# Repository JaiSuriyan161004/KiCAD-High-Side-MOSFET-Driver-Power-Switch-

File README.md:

# High-Side MOSFET Solid-State Switch PCB Prototype

A discrete power electronics hardware layout and component validation project implementing a logic-level triggered, high-side power switching architecture for high-current DC loads, featuring strict front/back electrical layer isolation.

## Project Overview & Technical Scope
The goal of this design was to transition from mechanical switching arrays to solid-state load isolation topologies using KiCad EDA. The circuit employs a logic-level P-channel MOSFET paired with a small-signal N-channel MOSFET driver network to switch a high-current 12V DC barrel jack output line safely. This structure allows low-voltage, low-current microcontroller pins (3.3V/5V logic) to isolate and actuate heavy inductive or resistive DC peripheral loads without exposing control logic to high-power rails.

## Core Engineering Objectives
* **Double-Sided Power & Signal Isolation Layout:** Implemented a strict component separation strategy to optimize noise immunity and thermal performance. **High-current power delivery components are populated exclusively on the front layer**, while **low-power control signal elements are placed entirely on the back layer**. This distinct physical partitioning prevents high-current return loops from corrupting weak control logic lines.
* **Semiconductor Parametric Optimization:** Evaluated manufacturer datasheets to analyze critical transfer characteristics, balancing Gate-Source Threshold Voltage ($V_{GS(th)}$) and Static Drain-Source On-Resistance ($R_{DS(on)}$) curves. This ensures full channel saturation from weak logic inputs to prevent thermal runaway.
* **Over-Engineering & Safety Margin Analysis:** Practiced safe industrial power design methods by picking power components whose Drain-Source Voltage ($V_{DS}$) and continuous drain current ($I_D$) limits exceed maximum load requirements by a strict 2x engineering safety factor.
* **Thermal Architecture & Packaging Design:** Studied the thermal layout profiles of Through-Hole Technology (THT) vs. Surface Mount Devices (SMD). Addressed thermal dissipation constraints by comparing bulky TO-220 packages against compact DPAK/SOIC-8 footprints that utilize dedicated PCB copper pours as thermal heatsinks.
* **Geometric Power Trace Layout:** Configured high-current routing lines with widened trace cross-sections to minimize parasitic resistance and voltage drops across primary power delivery tracks.

## Project Status: Design Phase (Digital Prototype)
*Note: This project is maintained digitally within KiCad to validate custom design rules, trace geometries, and schematic-to-board footprint synchronizations prior to physical prototyping loops.*

---

## Design Visual Previews

### 1. Circuit Schematic Diagram
*Capture of the high-side power distribution configuration, small-signal control isolation layer, and input/output DC terminals.*

### 2. 3D Visual Board Render (Front View - Power Stage)
*Complete 3D structural render showing power footprint clearances, structural trace widths, and heavy-current hardware components populated on the primary layer.*

### 3. 3D Visual Board Render (Back View - Low Power Logic Stage)
*Complete 3D structural render showing the reverse side of the board dedicated entirely to clean, low-current logic and control signal traces.*

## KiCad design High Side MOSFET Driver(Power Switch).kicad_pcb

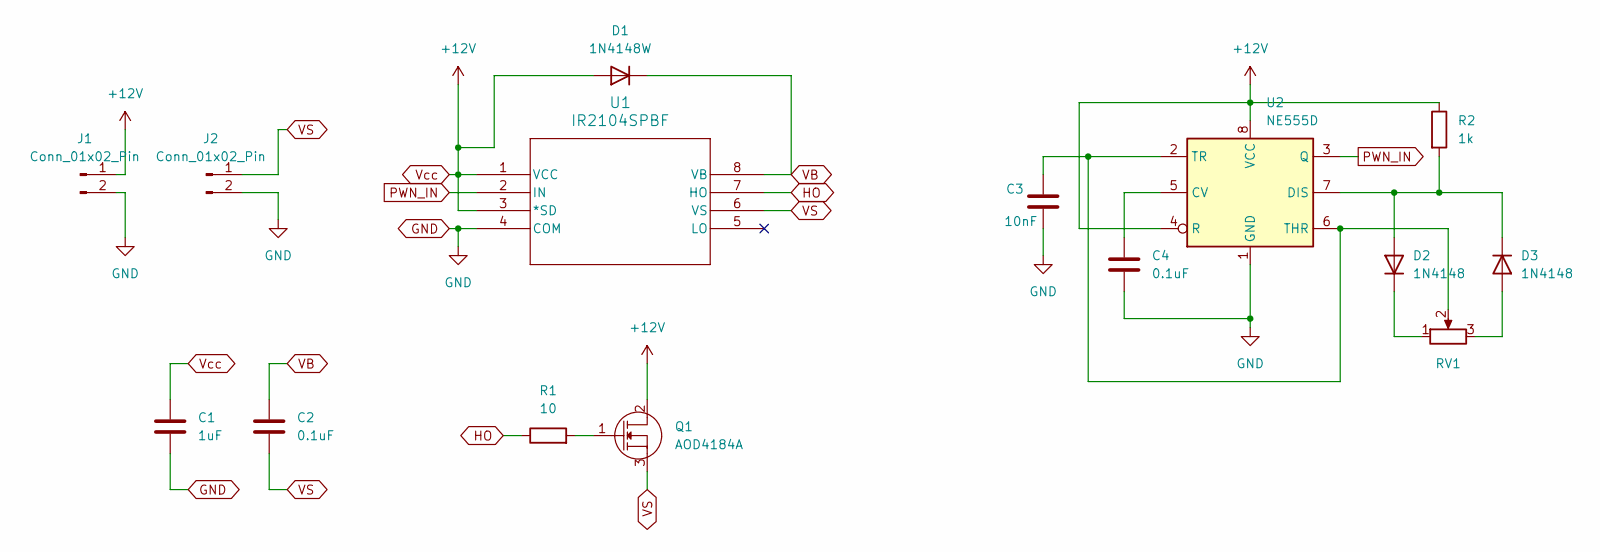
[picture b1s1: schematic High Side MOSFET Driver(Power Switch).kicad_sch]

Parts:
C1: 1uF; C_0201_0603Metric
C2, C4: 0.1uF; C_0201_0603Metric
C3: 10nF; C_0201_0603Metric
D1: 1N4148W; D_SOD-123
D2, D3: 1N4148; D_SOD-123
J1, J2: Conn_01x02_Pin; JWT_A3963_1x02_P3.96mm_Vertical
Q1: AOD4184A; TO-252-2
R1: 10; R_0201_0603Metric
R2: 1k; R_0201_0603Metric
RV1: R_Potentiometer; Potentiometer_Bourns_3314G_Vertical
U1: IR2104SPBF; SOIC-8_3.9x4.9mm_P1.27mm
U2: NE555D; SOIC-8_3.9x4.9mm_P1.27mm

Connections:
GND: C1.2, C3.2, C4.2, J1.2, J2.2, U1.4 (COM), U2.1 (GND)
HO: R1.1, U1.7 (HO)
unnamed: D2.2 (A), D3.1 (K), R2.2, U2.7 (DIS)
unnamed: D2.1 (K), RV1.1
unnamed: D3.2 (A), RV1.3
unnamed: Q1.1 (G), R1.2
unnamed: C4.1, U2.5 (CV)
unnamed: C3.1, RV1.2, U2.2 (TR), U2.6 (THR)
PWN_IN: U1.2 (IN), U2.3 (Q)
VB: C2.1, D1.1 (K), U1.8 (VB)
VS: C2.2, J2.1, Q1.3 (S), U1.6 (VS)
Vcc: C1.1, D1.2 (A), J1.1, Q1.2 (D), R2.1, U1.1 (VCC), U1.3 (*SD), U2.4 (R), U2.8 (VCC)

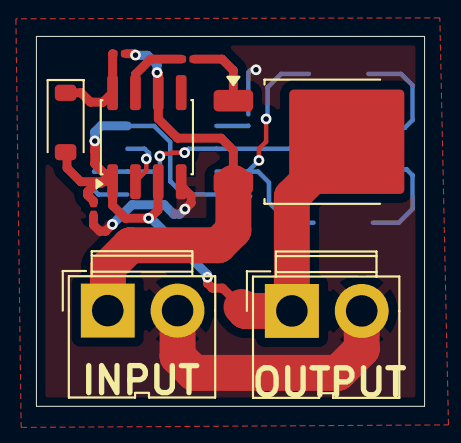
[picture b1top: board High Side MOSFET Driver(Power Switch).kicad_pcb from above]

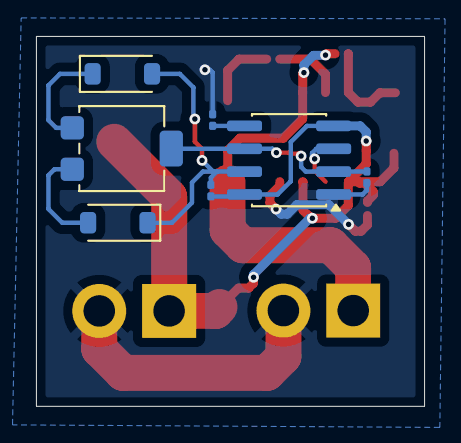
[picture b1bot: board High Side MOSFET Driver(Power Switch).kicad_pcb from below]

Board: 2 copper layers, 21.6 x 20.5 mm, 15 parts (7 on the bottom side), 12 nets.
